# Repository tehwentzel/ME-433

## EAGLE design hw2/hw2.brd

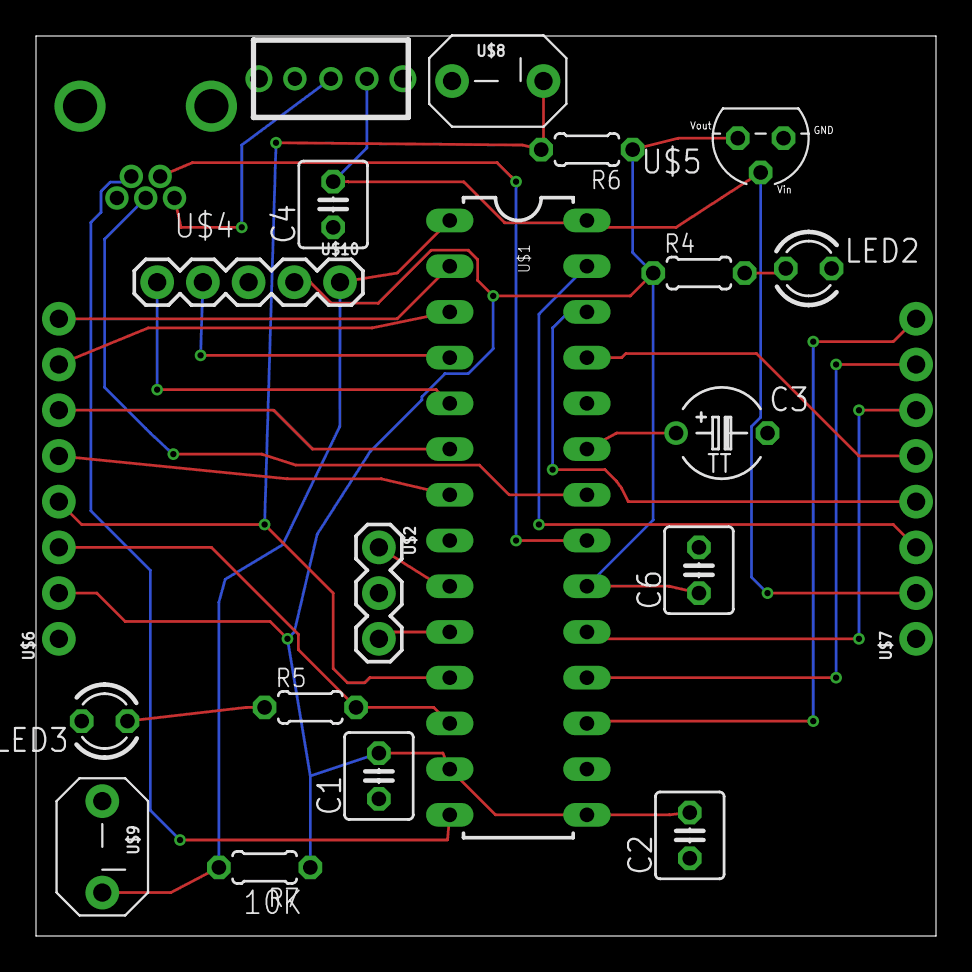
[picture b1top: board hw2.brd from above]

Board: 2 copper layers, 50.0 x 50.0 mm, 21 parts (0 on the bottom side), 27 nets.

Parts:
C1, C2, C4, C6: .1uF; C025-040X050
C3: 10uF; TAP5-50
LED2, LED3: LED3MM
R4, R5: 330; 0204/5
R6, R7: 10k; 0204/5
U$1: PIC32MX250F128B; DIL28-3
U$2: OSC; 1X03
U$3: SLIDESWITCH
U$4: USBCONNECTOR; USB-MB-H
U$5: MCP1702; TO92
U$6, U$7: CONN_8; 1X08
U$8, U$9: SWITCH
U$10: PICKIT_HEADER; 1X05

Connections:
14USBID/RB5: U$1.14, U$4.ID
21D+/RB10: U$1.21, U$4.D+
22D-/RB11: U$1.22, U$4.D-
!MCLR: R7.2, U$1.1, U$9.2, U$10.1
+3V3: C1.2, C2.2, C6.1, R4.1, R6.1, R7.1, U$1.13, U$1.23, U$1.28, U$5.3, U$6.2, U$10.2
+5V: C4.2, U$1.15, U$3.PIN3, U$5.2, U$7.2
GND: C1.1, C2.1, C3.-, C4.1, C6.2, LED2.K, LED3.K, U$1.8, U$1.19, U$1.27, U$2.2, U$4.GND, U$5.1, U$6.1, U$7.1, U$8.1, U$9.1, U$10.3
unnamed: U$1.10, U$2.3
unnamed: U$1.9, U$2.1
unnamed: C3.+, U$1.20
unnamed: LED2.A, R4.2
unnamed: LED3.A, R5.1
RA0: U$1.2, U$6.8
RA1: U$1.3, U$6.7
RA4: R5.2, U$1.12, U$6.3
RB0: U$1.4, U$10.4
RB1: U$1.5, U$10.5
RB2: U$1.6, U$6.6
RB3: U$1.7, U$6.5
RB4: R6.2, U$1.11, U$6.4, U$8.2
RB7: U$1.16, U$7.3
RB8: U$1.17, U$7.4
RB9: U$1.18, U$7.5
RB13: U$1.24, U$7.6
RB14: U$1.25, U$7.7
RB15: U$1.26, U$7.8
VBUS: U$3.PIN2, U$4.VBUS

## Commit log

2018-04-09 added circuit pictures
2018-04-09 added scope images
2018-04-10 added video
2018-04-10 added C ignore file
2018-04-10 fixed ignore file
2018-04-12 added eagle files
2018-04-12 first schematic
2018-04-17 gerber files made
2018-04-18 spi code working
2018-04-23 added I2C code
2018-04-24 added demo videos and schematic
2018-04-25 added hw6 code and video
2018-05-01 hw7 working
2018-05-01 fixed vector output for accelerometer data
2018-05-03 hw8 added
2018-05-07 hw9 working
2018-05-09 added code for hw10
2018-05-09 added extra graphic
2018-05-14 Added hw11
2018-05-17 hw12
2018-05-22 HW 13 Code
2018-05-24 hw14
2018-06-13 Added FInal project code
